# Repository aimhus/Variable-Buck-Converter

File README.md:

# Adjustable Voltage Step Down Board

## Functionality

- This PCB accepts inputs within a range of 16 V to 9 V and steps it down to a range between 9 V and 3.3 V
- Max Current of 1.5 A
- The user can choose the desired output voltage by adjusting the potentiometer
- All circuit component values were calculated to safely and efficiently step down voltage within the full range of input and output voltages
<br></br>
## Common Potentiometer Values
Here are some commonly desired output voltages and the corresponding potentiometer values:

| Output Voltage | Potentiometer Value |
| --- | --- |
| 9 V | 19 kΩ|
| 5 V | 9.2 kΩ |
| 3.3 V | 5.1 kΩ|  
      
<br></br>

## Schematics

### Board Layout Schematics:

<br></br>

### Floorplan:

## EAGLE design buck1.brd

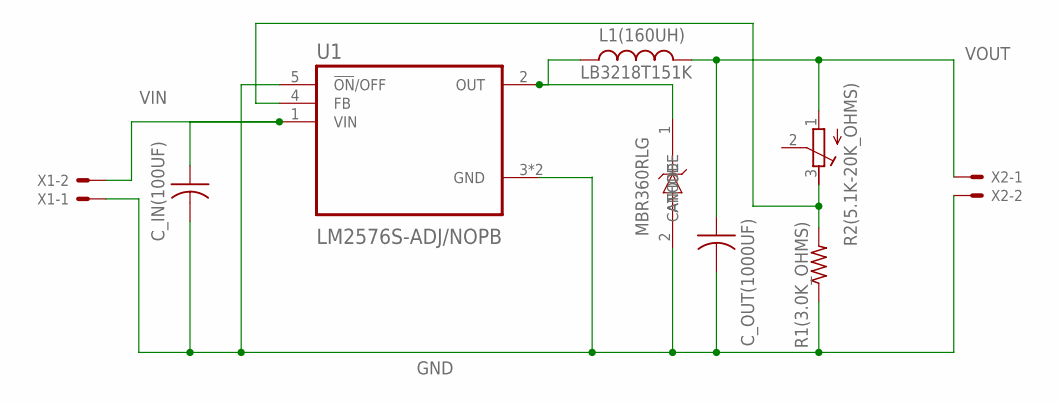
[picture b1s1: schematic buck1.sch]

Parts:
CR1: MBR360RLG; DO-201AD_ONS
C_IN(100UF): C-USC1206; C1206
C_OUT(1000UF): C-USC1206; C1206
L1(160UH): LB3218T151K; INDC3218X200N
R1(3.0K_OHMS): R-US_R1206; R1206
R2(5.1K-20K_OHMS): R-TRIMMTS63Z; RTRIMTS63Z
U1: LM2576S-ADJ/NOPB; VREG_TPS79625KTTR
X1, X2: 22-23-2021

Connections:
GND: CR1.2 (ANODE), C_IN(100UF).2, C_OUT(1000UF).2, R1(3.0K_OHMS).1, U1.3 (GND), U1.5 (!ON!/OFF), U1.6 (GND), X1.1, X2.2
unnamed: CR1.1 (CATHODE), L1(160UH).1, U1.2 (OUT)
unnamed: R1(3.0K_OHMS).2, R2(5.1K-20K_OHMS).3 (E), U1.4 (FB)
VIN: C_IN(100UF).1, U1.1 (VIN), X1.2
VOUT: C_OUT(1000UF).1, L1(160UH).2, R2(5.1K-20K_OHMS).1 (A), X2.1

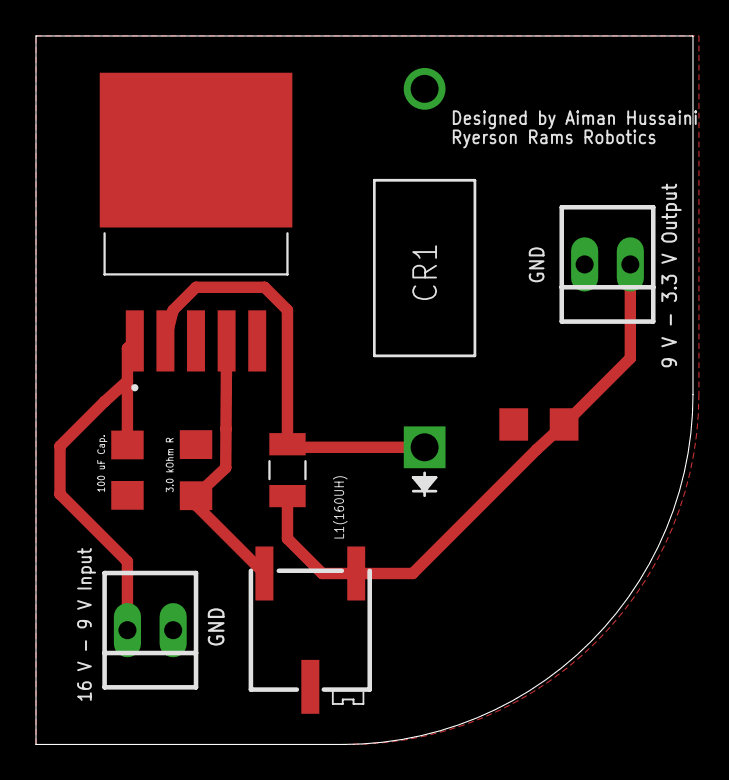
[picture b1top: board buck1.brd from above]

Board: 2 copper layers, 36.5 x 39.4 mm, 9 parts (0 on the bottom side), 5 nets.
